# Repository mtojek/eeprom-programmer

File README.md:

# eeprom-programmer
EEPROM programmer based on Arduino

This repository contains Kicad schematics and .ino source files to build the EEPROM programmer using Arduino UNO R3. If you are following the Ben's Eater course to [build a 6502 computer](https://eater.net/6502), you will see that Ben uses a [TL866 II Plus](https://eater.net/6502) model, but it is possible to program memory chips using this homebrew board.

## Sample output

Check Arduino serial monitor to see memory content:

```
Reset
Run!
0000: a9 ff 8d 02 60 a9 50 8d    00 60 6a 8d 00 60 4c 0a    ⸮⸮⸮`⸮P⸮ 
0010: 80 00 00 00 00 00 00 00    00 00 00 00 00 00 00 00    ⸮
0020: 00 00 00 00 00 00 00 00    00 00 00 00 00 00 00 00    
...
7fc0: 00 00 00 00 00 00 00 00    00 00 00 00 00 00 00 00    
7fd0: 00 00 00 00 00 00 00 00    00 00 00 00 00 00 00 00    
7fe0: 00 00 00 00 00 00 00 00    00 00 00 00 00 00 00 00    
7ff0: 00 00 00 00 00 00 00 00    00 00 00 00 00 80 00 00    
```

## Kicad preview

## Photos

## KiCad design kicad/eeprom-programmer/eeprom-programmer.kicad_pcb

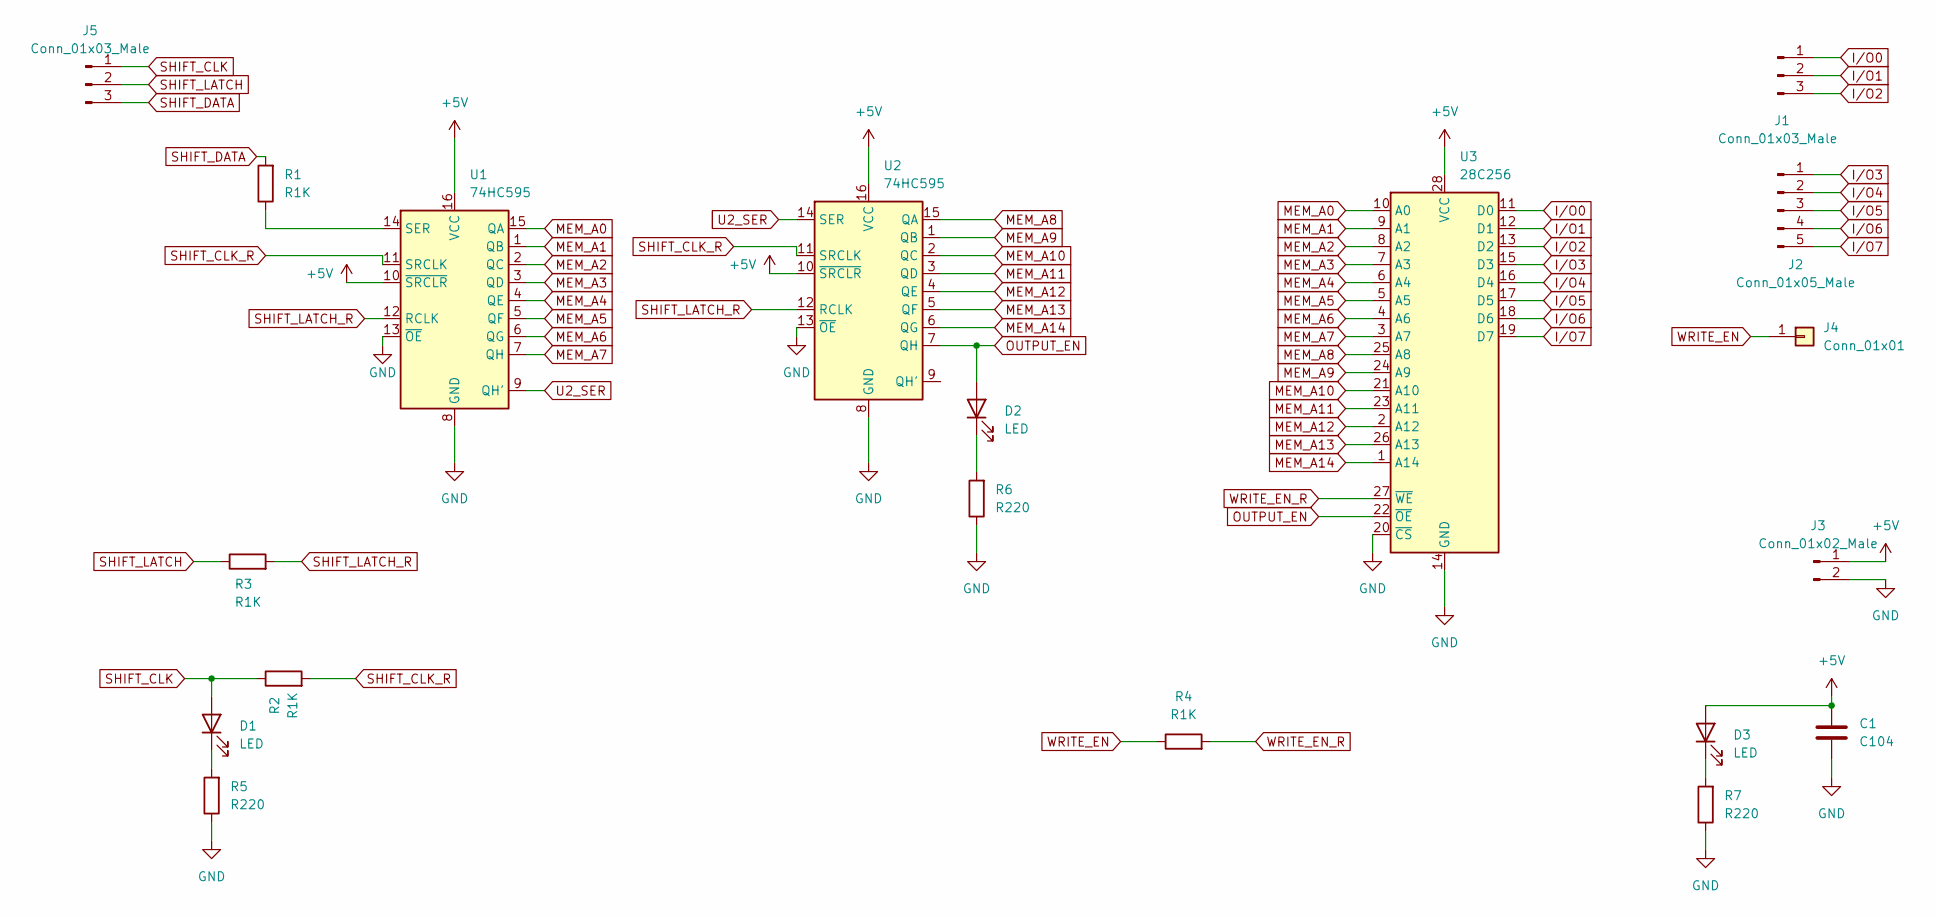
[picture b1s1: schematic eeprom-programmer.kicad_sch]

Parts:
C1: C104; C_Disc_D7.5mm_W2.5mm_P5.00mm
D1, D2, D3: LED; LED_D5.0mm
J1, J5: Conn_01x03_Male; PinHeader_1x03_P2.54mm_Vertical
J2: Conn_01x05_Male; PinHeader_1x05_P2.54mm_Vertical
J3: Conn_01x02_Male; PinHeader_1x02_P2.54mm_Vertical
J4: Conn_01x01; PinHeader_1x01_P2.54mm_Vertical
R1, R2, R3, R4: R1K; R_Axial_DIN0411_L9.9mm_D3.6mm_P12.70mm_Horizontal
R5, R6, R7: R220; R_Axial_DIN0411_L9.9mm_D3.6mm_P12.70mm_Horizontal
U1, U2: 74HC595; DIP-16_W7.62mm_Socket_LongPads
U3: 28C256; DIP-28_W15.24mm_Socket_LongPads

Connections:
+5V: C1.1, D3.2 (A), J3.1, U1.10 (~SRCLR), U1.16 (VCC), U2.10 (~SRCLR), U2.16 (VCC), U3.28 (VCC)
GND: C1.2, J3.2, R5.1, R6.1, R7.1, U1.8 (GND), U1.13 (~OE), U2.8 (GND), U2.13 (~OE), U3.14 (GND), U3.20 (~CS)
I/O0: J1.1, U3.11 (D0)
I/O1: J1.2, U3.12 (D1)
I/O2: J1.3, U3.13 (D2)
I/O3: J2.1, U3.15 (D3)
I/O4: J2.2, U3.16 (D4)
I/O5: J2.3, U3.17 (D5)
I/O6: J2.4, U3.18 (D6)
I/O7: J2.5, U3.19 (D7)
MEM_A0: U1.15 (QA), U3.10 (A0)
MEM_A1: U1.1 (QB), U3.9 (A1)
MEM_A2: U1.2 (QC), U3.8 (A2)
MEM_A3: U1.3 (QD), U3.7 (A3)
MEM_A4: U1.4 (QE), U3.6 (A4)
MEM_A5: U1.5 (QF), U3.5 (A5)
MEM_A6: U1.6 (QG), U3.4 (A6)
MEM_A7: U1.7 (QH), U3.3 (A7)
MEM_A8: U2.15 (QA), U3.25 (A8)
MEM_A9: U2.1 (QB), U3.24 (A9)
MEM_A10: U2.2 (QC), U3.21 (A10)
MEM_A11: U2.3 (QD), U3.23 (A11)
MEM_A12: U2.4 (QE), U3.2 (A12)
MEM_A13: U2.5 (QF), U3.26 (A13)
MEM_A14: U2.6 (QG), U3.1 (A14)
unnamed: D1.1 (K), R5.2
unnamed: D3.1 (K), R7.2
unnamed: D2.1 (K), R6.2
unnamed: R1.1, U1.14 (SER)
OUTPUT_EN: D2.2 (A), U2.7 (QH), U3.22 (~OE)
SHIFT_CLK: D1.2 (A), J5.1, R2.1
SHIFT_CLK_R: R2.2, U1.11 (SRCLK), U2.11 (SRCLK)
SHIFT_DATA: J5.3, R1.2
SHIFT_LATCH: J5.2, R3.1
SHIFT_LATCH_R: R3.2, U1.12 (RCLK), U2.12 (RCLK)
U2_SER: U1.9 (QH'), U2.14 (SER)
WRITE_EN: J4.1, R4.1
WRITE_EN_R: R4.2, U3.27 (~WE)

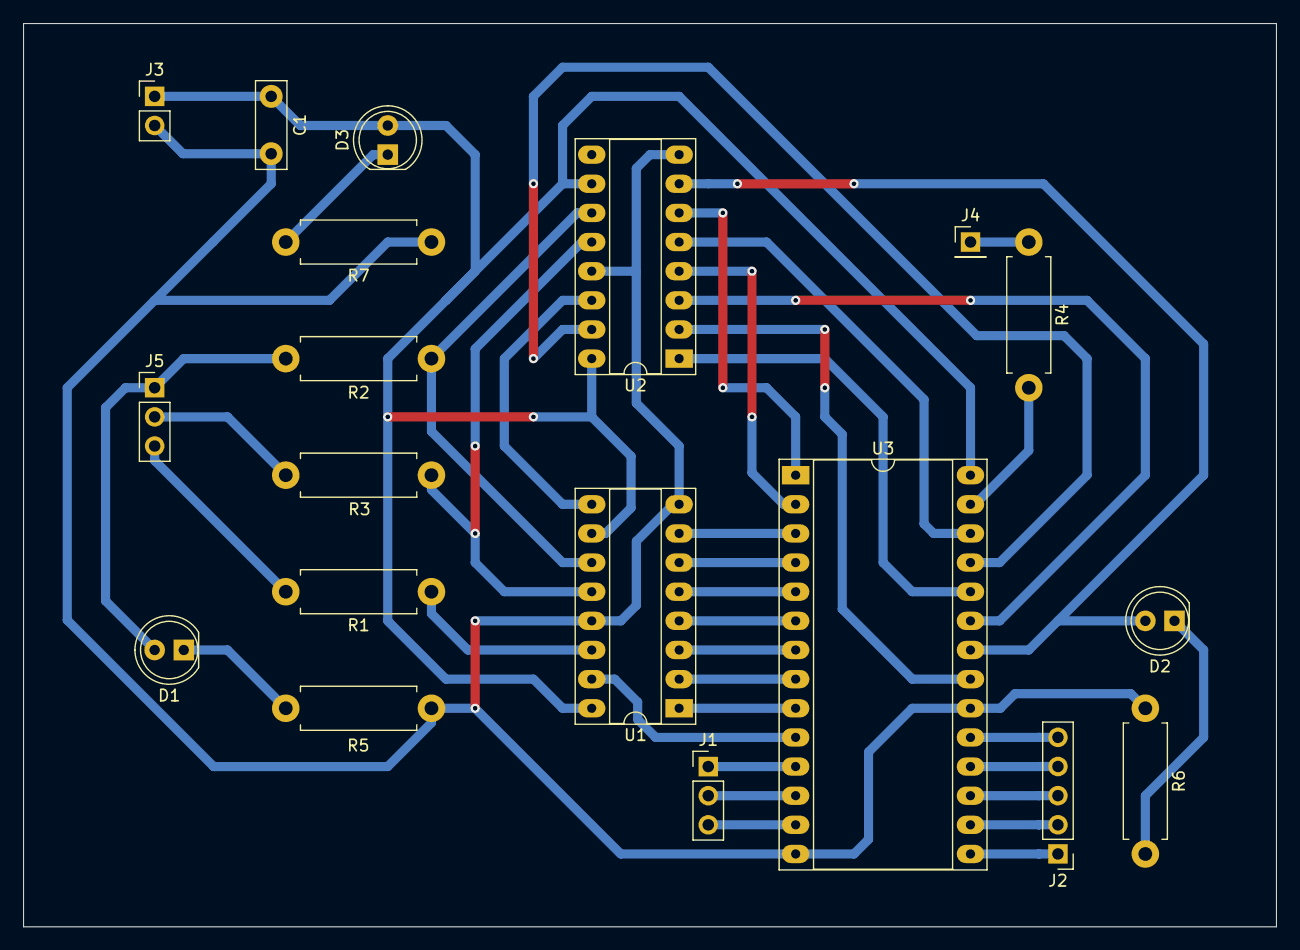
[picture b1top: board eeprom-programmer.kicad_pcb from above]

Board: 2 copper layers, 109.2 x 78.7 mm, 19 parts (0 on the bottom side), 38 nets.

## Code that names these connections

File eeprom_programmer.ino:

#define SHIFT_CLK 2
#define SHIFT_LATCH 3
#define SHIFT_DATA 4

#define EEPROM_D0 5
#define EEPROM_D7 12

#define WRITE_EN 13

#define OPCODE_BRK 0

void setAddress(unsigned int address, bool outputEnable) {
  digitalWrite(SHIFT_LATCH, LOW);
  shiftOut(SHIFT_DATA, SHIFT_CLK, MSBFIRST, (address >> 8) | (outputEnable ? 0 : 0x80));
  shiftOut(SHIFT_DATA, SHIFT_CLK, MSBFIRST, address);
  digitalWrite(SHIFT_LATCH, HIGH);
  digitalWrite(SHIFT_LATCH, LOW);
}

byte readEEPROM(unsigned int address) {
  for (int pin = EEPROM_D0; pin <= EEPROM_D7; pin += 1) {
    pinMode(pin, INPUT);
  }

  setAddress(address, true);
  byte data = 0;
  for (int pin = EEPROM_D7; pin >= EEPROM_D0; pin -= 1) {
    data = (data << 1) + digitalRead(pin);
  }
  return data;
}

byte writeEEPROM(unsigned int address, byte data) {
  for (int pin = EEPROM_D0; pin <= EEPROM_D7; pin += 1) {
    pinMode(pin, OUTPUT);
  }

  setAddress(address, false);
  for (int pin = EEPROM_D0; pin <= EEPROM_D7; pin += 1) {
    digitalWrite(pin, data & 1);
    data = data >> 1;
  }
  digitalWrite(WRITE_EN, LOW);
  delayMicroseconds(1);
  digitalWrite(WRITE_EN, HIGH);
  delay(10);
}

void printContents(unsigned int offset, unsigned int len) {
  for (unsigned int base = offset; base <= offset + len; base += 16) {
    byte data[16];
    for (unsigned int offset = 0; offset < 16; offset += 1) {
      data[offset] = readEEPROM(base + offset);
    }

    char buf[80];
    sprintf(buf, "%04x: %02x %02x %02x %02x %02x %02x %02x %02x    %02x %02x %02x %02x %02x %02x %02x %02x    %c%c%c%c%c%c%c%c %c%c%c%c%c%c%c%c",
            base,
            data[0], data[1], data[2], data[3], data[4], data[5], data[6], data[7], data[8], data[9], data[10], data[11], data[12], data[13], data[14], data[15],
            data[0], data[1], data[2], data[3], data[4], data[5], data[6], data[7], data[8], data[9], data[10], data[11], data[12], data[13], data[14], data[15]);
    Serial.println(buf);
  }
}

void setup() {
  pinMode(SHIFT_CLK, OUTPUT);
  pinMode(SHIFT_LATCH, OUTPUT);
  pinMode(SHIFT_DATA, OUTPUT);

  digitalWrite(WRITE_EN, HIGH);
  pinMode(WRITE_EN, OUTPUT);

  Serial.begin(57600);

  Serial.println("Reset");
  delay(2000);
  Serial.println("Run!");

  unsigned int offset = 0;
  char program[] = {
0xa9, 0xff, 0x8d, 0x03, 0x60, 0xa9, 0x00, 0x8d, 0x01, 0x60, 0x85, 0x04, 0x20, 0x27, 0x80, 0x38,
0xa5, 0x00, 0xe5, 0x04, 0xc9, 0x19, 0x90, 0xf7, 0xa9, 0x01, 0x4d, 0x01, 0x60, 0x8d, 0x01, 0x60,
0xa5, 0x00, 0x85, 0x04, 0x4c, 0x0f, 0x80, 0xa9, 0x00, 0x85, 0x00, 0x85, 0x01, 0x85, 0x02, 0x85,
0x03, 0xa9, 0x40, 0x8d, 0x0b, 0x60, 0xa9, 0x80, 0x8d, 0x04, 0x60, 0xa9, 0x00, 0x8d, 0x05, 0x60,
0xa9, 0xc0, 0x8d, 0x0e, 0x60, 0x58, 0x60, 0x2c, 0x04, 0x60, 0xe6, 0x00, 0xd0, 0x0a, 0xe6, 0x01,
0xd0, 0x06, 0xe6, 0x02, 0xd0, 0x02, 0xe6, 0x03, 0x40, 0x00, 0x00, 0x00, 0x00, 0x00, 0x00, 0x00
  };
  const int programLen = 16 * 6;

  for (offset = 0; offset <= programLen; offset++) {
    writeEEPROM(offset, program[offset]);
  }

  // Fill empty bytes
  /*for (offset = 0x7f00; offset < 0x7ffc; offset++) {
    writeEEPROM(offset, OPCODE_BRK);
    }*/

  // Write vector
  /*writeEEPROM(0x7ffa, 0x00);
  writeEEPROM(0x7ffb, 0x00);

  writeEEPROM(0x7ffc, 0x00);
  writeEEPROM(0x7ffd, 0x80);

  writeEEPROM(0x7ffe, 0x47);
  writeEEPROM(0x7fff, 0x80);*/

  printContents(0, 0x130);
  printContents(0x7f00, 0xff);
}


void loop() {
  // put your main code here, to run repeatedly:

}

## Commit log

2022-02-20 PoC read/write eeprom
2022-02-27 Kicad WIP
2022-03-06 PCB ready
2022-03-06 PCB polished
2022-03-06 Resize
2022-03-06 Refactor
2022-03-13 Write hello_world to eeprom
2022-03-25 Screenshots
2022-03-25 Images
2022-03-25 Rename
2022-03-25 Log file not needed anymore
2022-10-13 Backup
